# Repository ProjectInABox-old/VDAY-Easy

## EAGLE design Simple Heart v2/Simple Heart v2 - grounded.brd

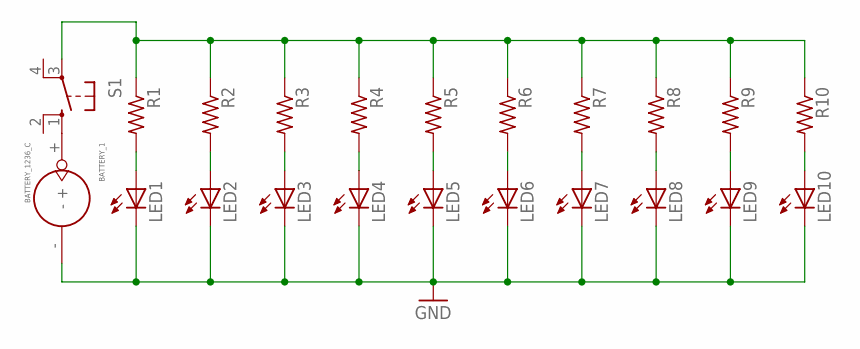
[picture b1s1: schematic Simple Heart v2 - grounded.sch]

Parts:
BATTERY_1: BATTERY_1236_C
LED1, LED2, LED3, LED4, LED5, LED6, LED7, LED8, LED9, LED10: LED5MM
R1, R2, R3, R4, R5, R6, R7, R8, R9, R10: R-US_0204/7; 0204/7
S1: 10-XX; B3F-10XX

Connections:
GND: BATTERY_1.-, LED1.K (C), LED2.K (C), LED3.K (C), LED4.K (C), LED5.K (C), LED6.K (C), LED7.K (C), LED8.K (C), LED9.K (C), LED10.K (C)
unnamed: LED1.A, R1.2
unnamed: LED2.A, R2.2
unnamed: LED3.A, R3.2
unnamed: LED4.A, R4.2
unnamed: LED5.A, R5.2
unnamed: LED6.A, R6.2
unnamed: LED7.A, R7.2
unnamed: LED8.A, R8.2
unnamed: LED9.A, R9.2
unnamed: LED10.A, R10.2
unnamed: BATTERY_1.+, S1.1 (S)
unnamed: R1.1, R2.1, R3.1, R4.1, R5.1, R6.1, R7.1, R8.1, R9.1, R10.1, S1.3

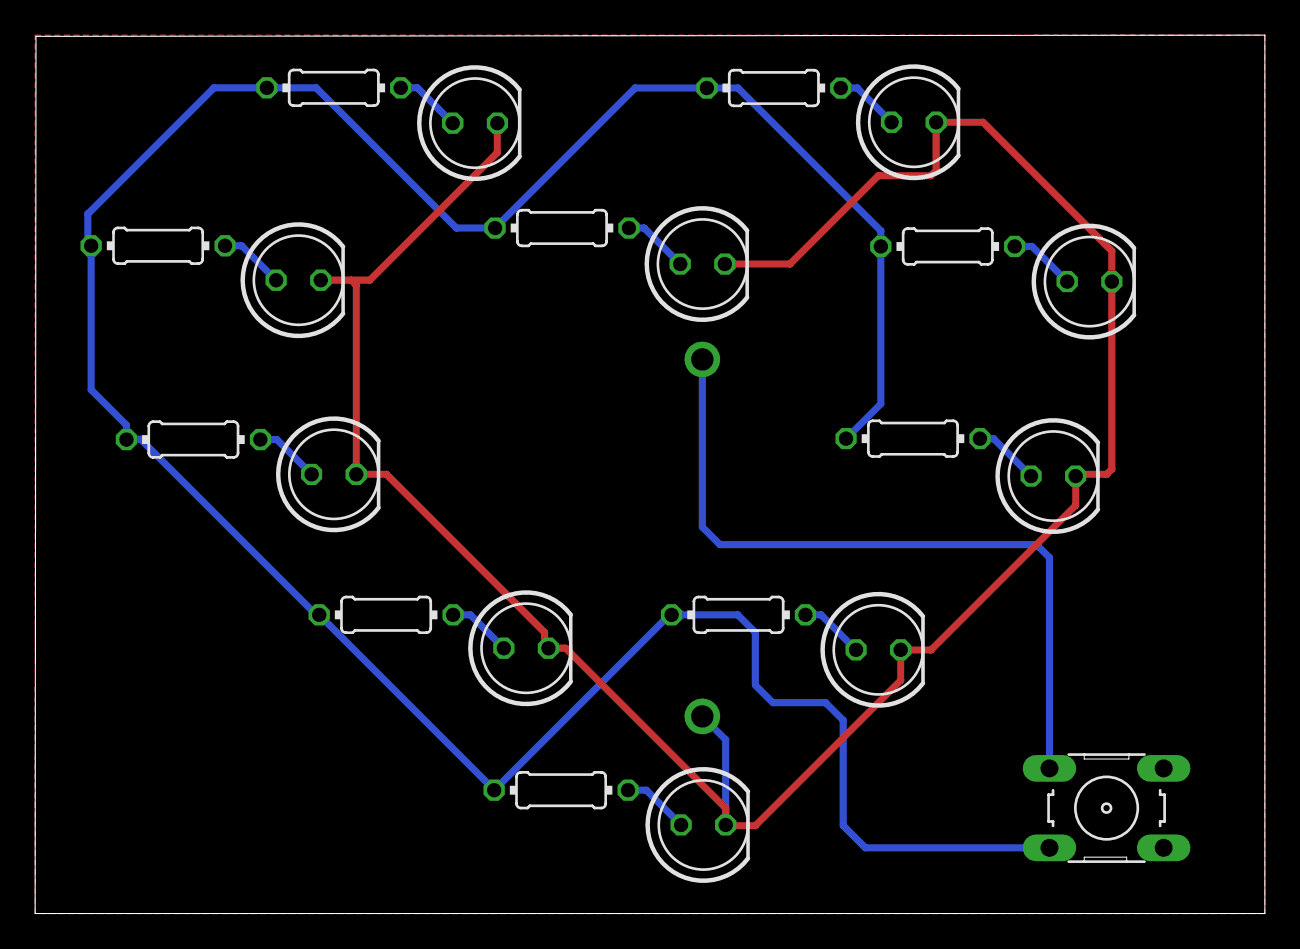
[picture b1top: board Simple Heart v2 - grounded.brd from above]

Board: 2 copper layers, 70.0 x 50.0 mm, 22 parts (1 on the bottom side), 13 nets.

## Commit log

2016-07-07 Redo routing in -grounded.
2016-07-07 Moving switch location a bit, added oshpark image. Need to confirm text.
2016-07-07 OCDing on the power line routing...it's not symetrical yet. But closer.
